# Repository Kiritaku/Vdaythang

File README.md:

# Vdaythang
just a simple board with some leds

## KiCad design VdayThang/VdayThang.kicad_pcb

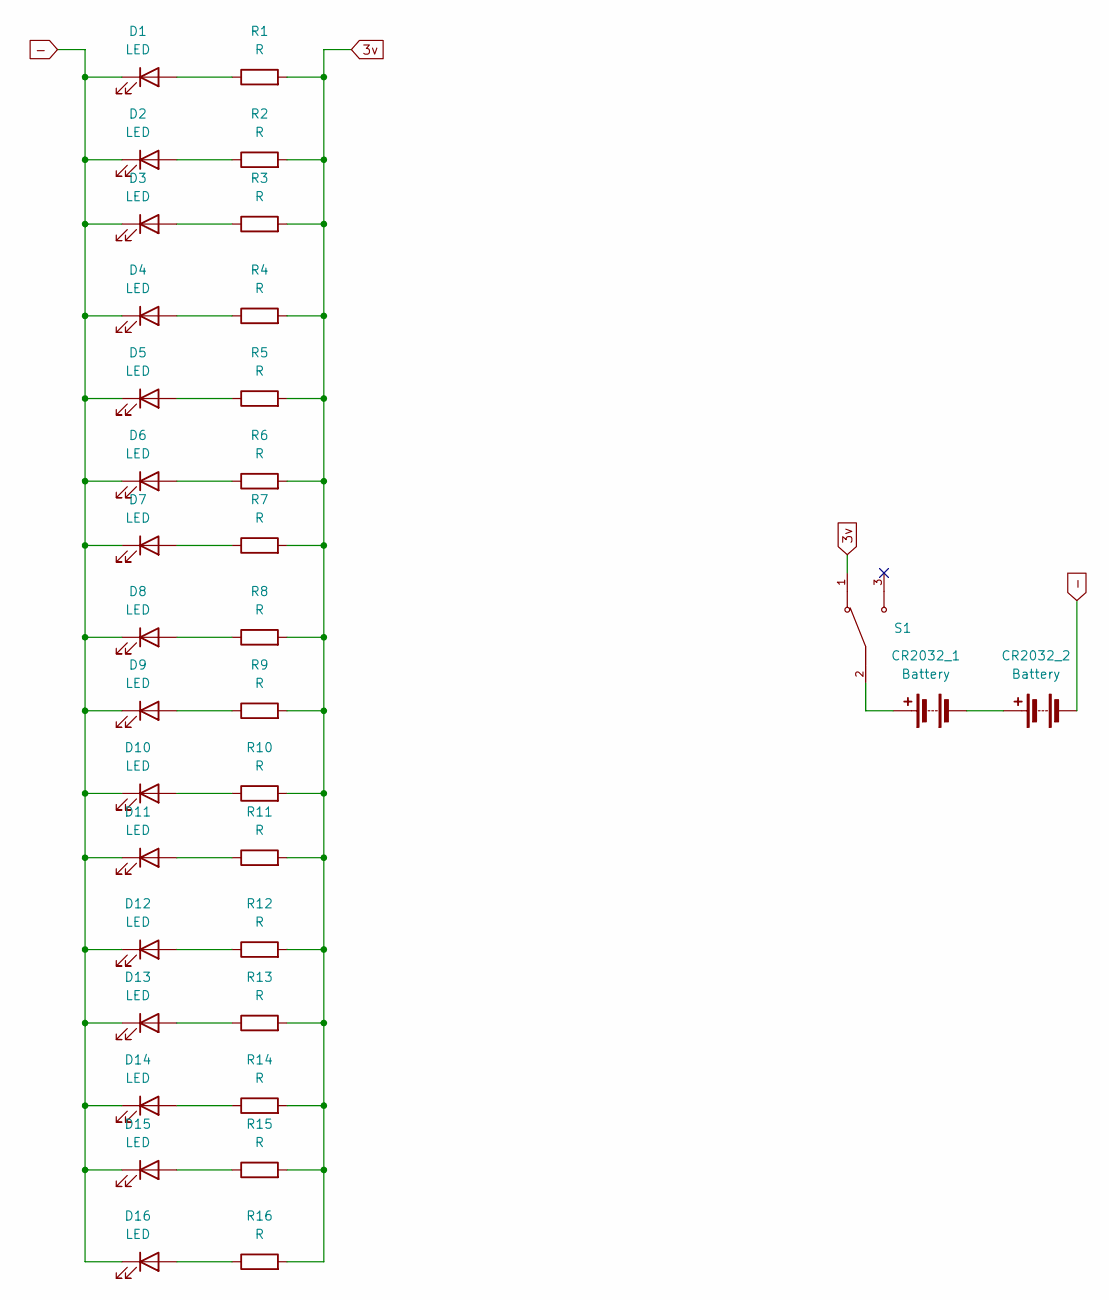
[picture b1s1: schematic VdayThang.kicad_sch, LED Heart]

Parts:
CR2032_1, CR2032_2: Battery; BAT_CR2032
D1, D2, D3, D4, D5, D6, D7, D8, D9, D10, D11, D12, D13, D14, D15, D16: LED; LED_0805_2012Metric
R1, R2, R3, R4, R5, R6, R7, R8, R9, R10, R11, R12, R13, R14, R15, R16: R; R_0805_2012Metric
S1: SW_SLW-66527511-SMT-TR; PARTREV 1.01

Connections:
3v: R1.2, R2.2, R3.2, R4.2, R5.2, R6.2, R7.2, R8.2, R9.2, R10.2, R11.2, R12.2, R13.2, R14.2, R15.2, R16.2, S1.1
-: CR2032_2.2 (-), D1.1 (K), D2.1 (K), D3.1 (K), D4.1 (K), D5.1 (K), D6.1 (K), D7.1 (K), D8.1 (K), D9.1 (K), D10.1 (K), D11.1 (K), D12.1 (K), D13.1 (K), D14.1 (K), D15.1 (K), D16.1 (K)
unnamed: CR2032_1.1 (+), S1.2
unnamed: CR2032_1.2 (-), CR2032_2.1 (+)
unnamed: D1.2 (A), R1.1
unnamed: D2.2 (A), R2.1
unnamed: D3.2 (A), R3.1
unnamed: D4.2 (A), R4.1
unnamed: D5.2 (A), R5.1
unnamed: D6.2 (A), R6.1
unnamed: D7.2 (A), R7.1
unnamed: D8.2 (A), R8.1
unnamed: D9.2 (A), R9.1
unnamed: D10.2 (A), R10.1
unnamed: D11.2 (A), R11.1
unnamed: D12.2 (A), R12.1
unnamed: D13.2 (A), R13.1
unnamed: D14.2 (A), R14.1
unnamed: D15.2 (A), R15.1
unnamed: D16.2 (A), R16.1

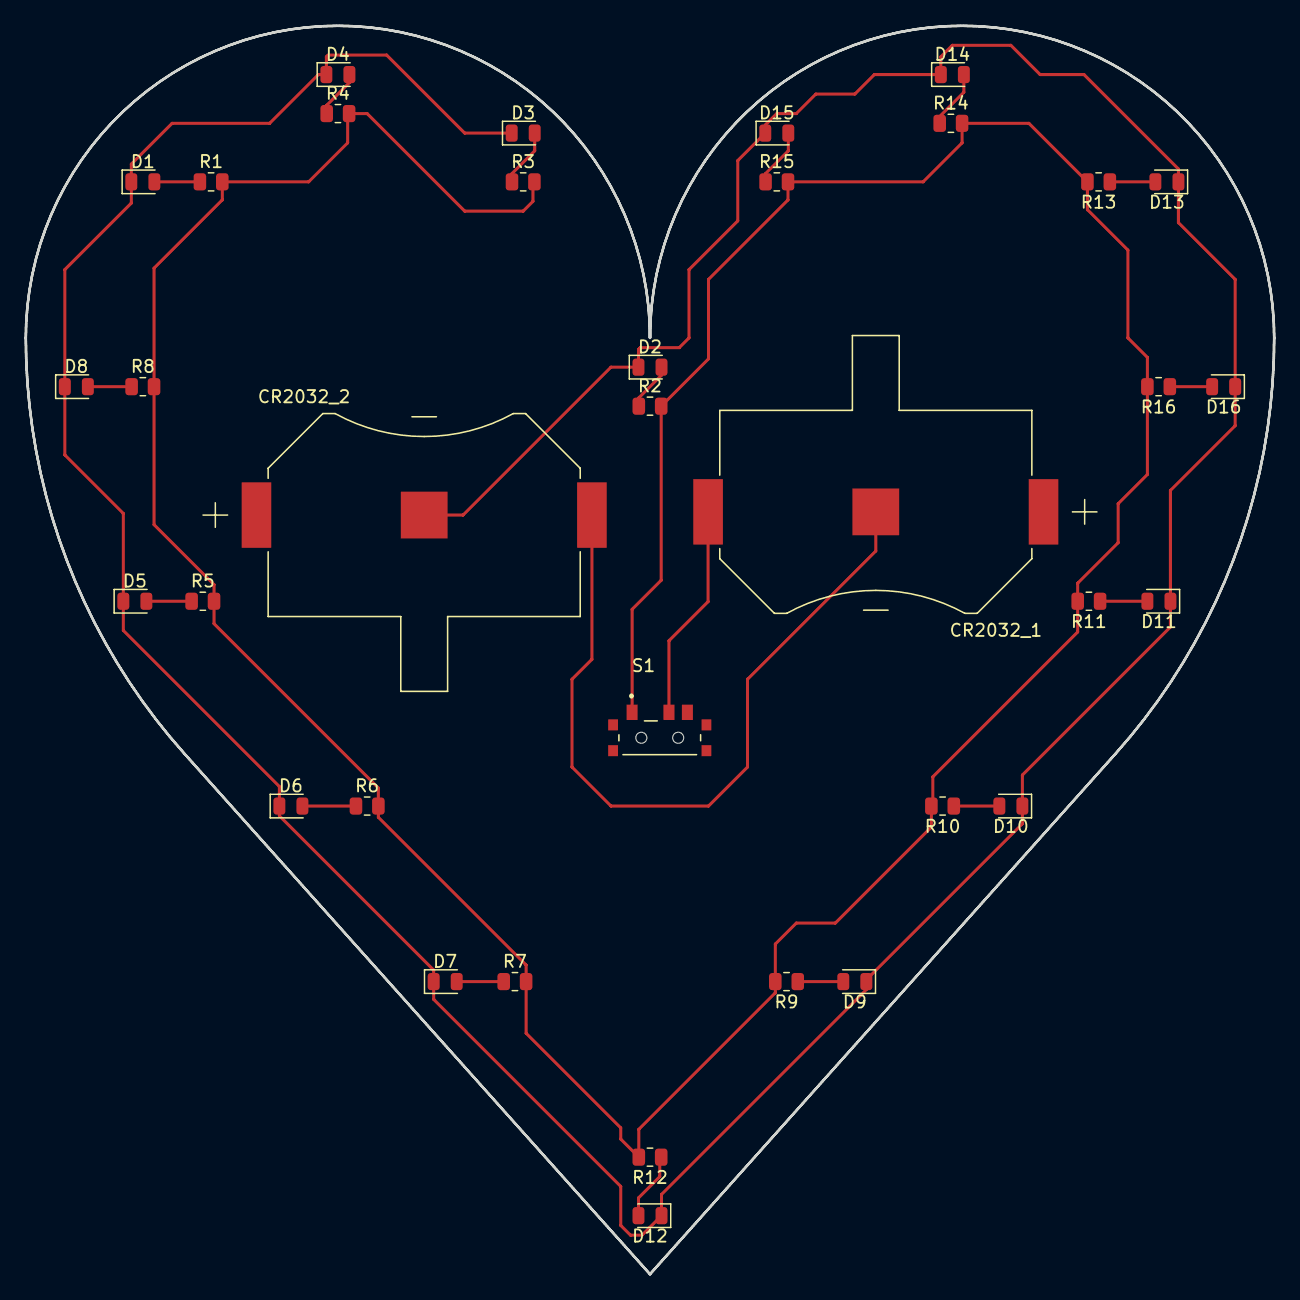
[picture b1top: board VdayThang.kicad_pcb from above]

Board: 2 copper layers, 101.6 x 101.6 mm, 35 parts (0 on the bottom side), 20 nets.

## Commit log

2025-02-03 project initialization
2025-02-03 Edge Cuts & Schematic
    Edge cuts made and imported. Most components placed on schematic.
2025-02-03 Schematic Mostly Done
    Still need to assign footprints
2025-02-04 assigned footprints
    assigned footprints
2025-02-04 placed footprints
    finished basic footprint layout
2025-02-04 Routing and Footprints done
    Finished routing board, made cr2032 holder footprint. Still need to add edge cuts.
2025-02-05 Finished :0
    layout done, BOM done, just need to print, etch, assemble
2025-02-11 Created etch file
    made a paste and pad file to use for etching
